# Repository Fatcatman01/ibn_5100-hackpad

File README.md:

# ibn_5100-hackpad

# Hackpad

# Schematic

# PCB

# Case

# BOM:
# Seeed XIAO RP2040
# 7x MX-Style switches
# EC11 Rotary encoder
# 7x Blank DSA keycaps
# 4x M3x5mx4mm heatset inserts
# 4x M3x10mm+5mm Male standoff
# 4x M3x5mm screws

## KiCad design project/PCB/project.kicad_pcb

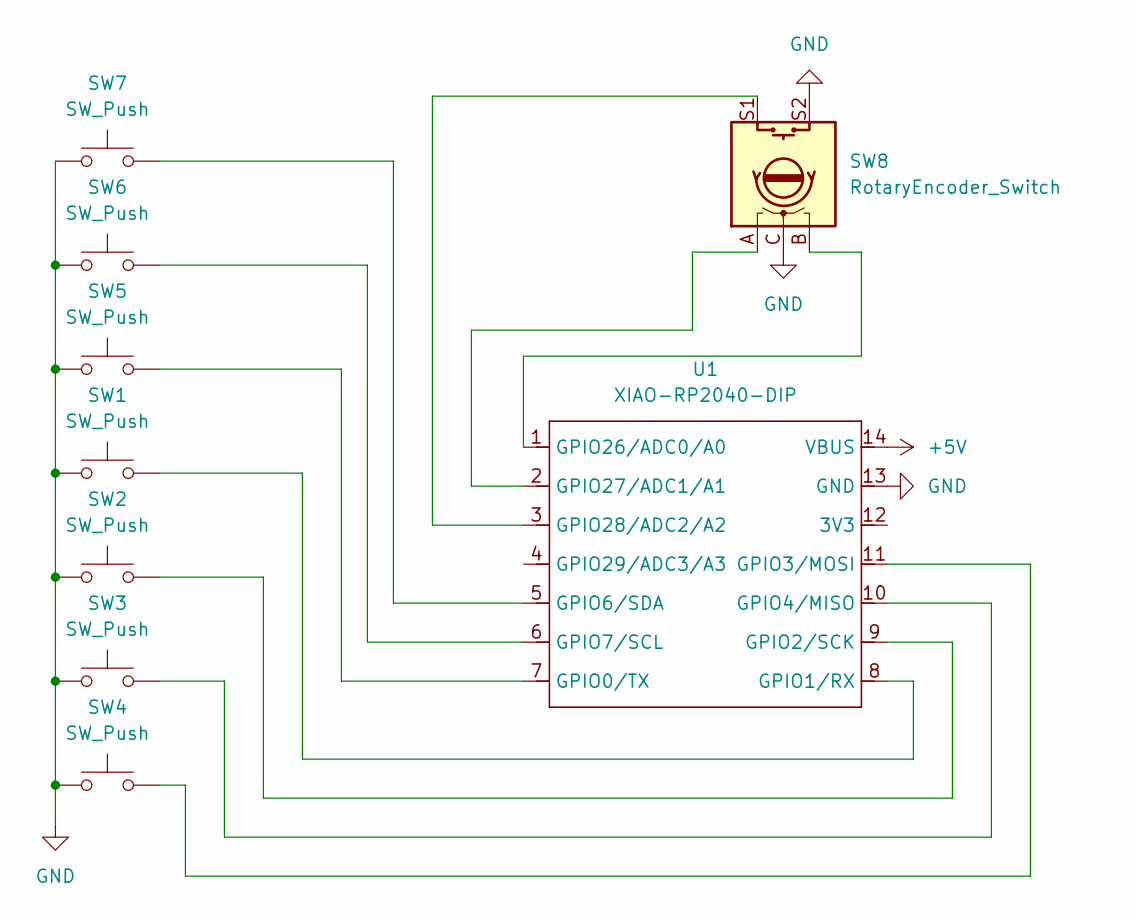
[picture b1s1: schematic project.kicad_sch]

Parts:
SW1, SW2, SW3, SW4, SW5, SW6, SW7: SW_Push; SW_Cherry_MX_1.00u_PCB
SW8: RotaryEncoder_Switch; RotaryEncoder_Alps_EC11E-Switch_Vertical_H20mm
U1: XIAO-RP2040-DIP

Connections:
+5V: U1.14 (VBUS)
GND: SW1.1, SW2.1, SW3.1, SW4.1, SW5.1, SW6.1, SW7.1, SW8.C, SW8.S2, U1.13 (GND)
unnamed: SW5.2, U1.7 (GPIO0/TX)
unnamed: SW1.2, U1.8 (GPIO1/RX)
unnamed: SW2.2, U1.9 (GPIO2/SCK)
unnamed: SW4.2, U1.11 (GPIO3/MOSI)
unnamed: SW3.2, U1.10 (GPIO4/MISO)
unnamed: SW7.2, U1.5 (GPIO6/SDA)
unnamed: SW6.2, U1.6 (GPIO7/SCL)
unnamed: SW8.B, U1.1 (GPIO26/ADC0/A0)
unnamed: SW8.A, U1.2 (GPIO27/ADC1/A1)
unnamed: SW8.S1, U1.3 (GPIO28/ADC2/A2)

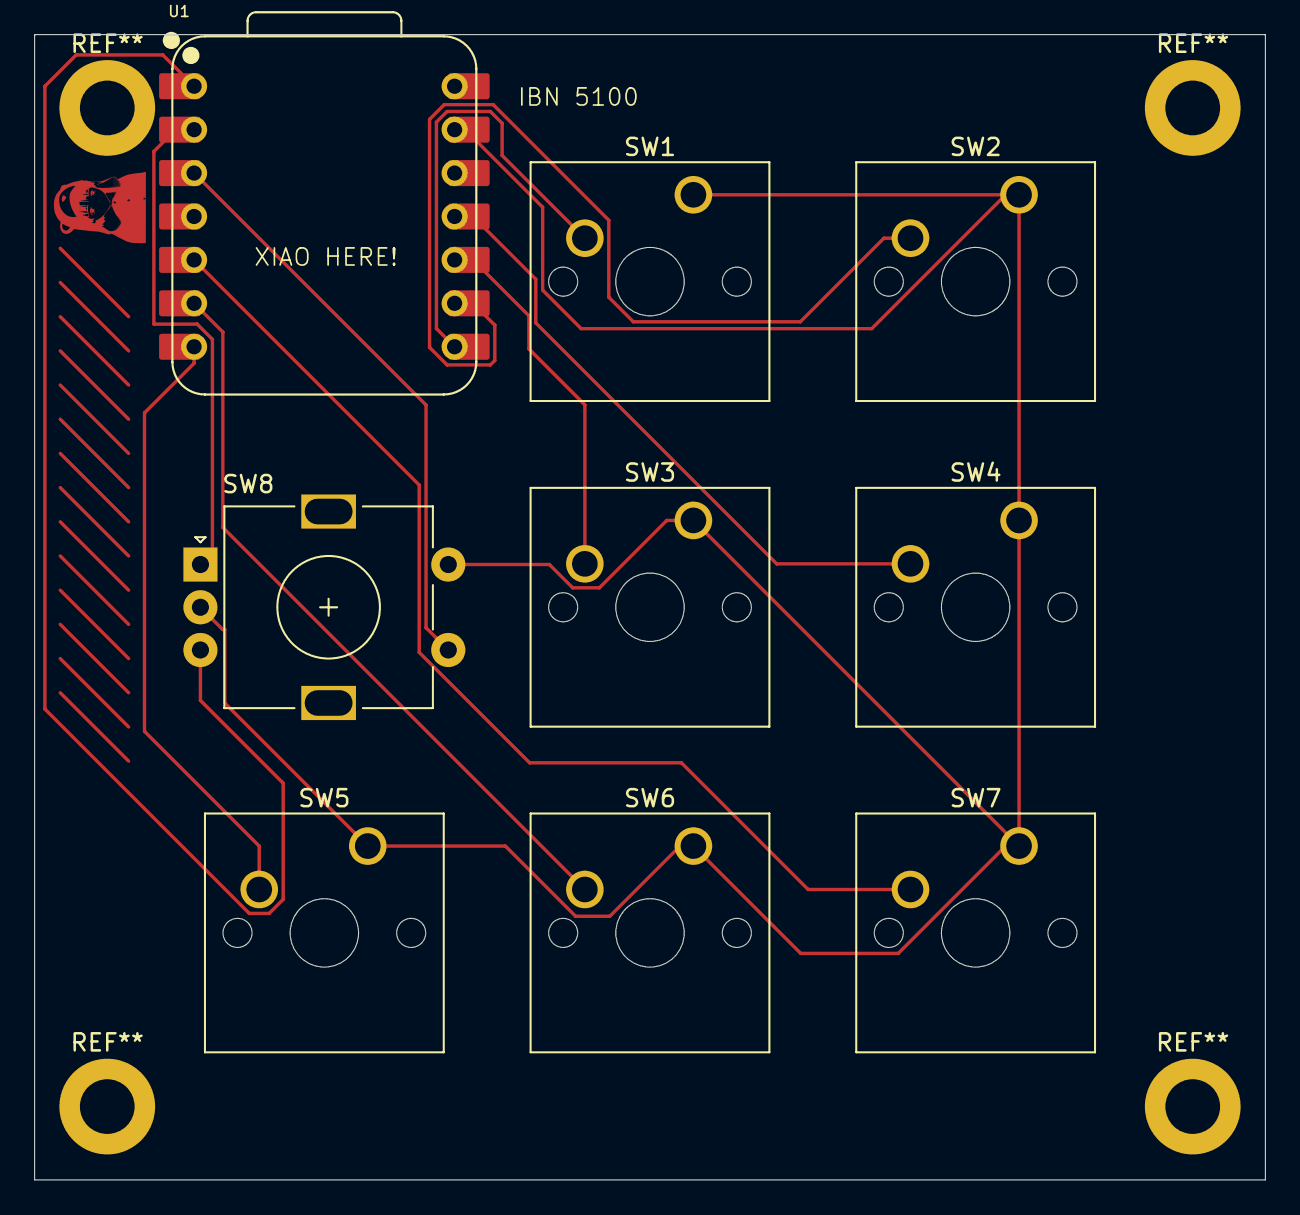
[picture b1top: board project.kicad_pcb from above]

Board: 2 copper layers, 72.0 x 67.0 mm, 9 parts (0 on the bottom side), 11 nets.

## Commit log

2025-12-07 Add README
